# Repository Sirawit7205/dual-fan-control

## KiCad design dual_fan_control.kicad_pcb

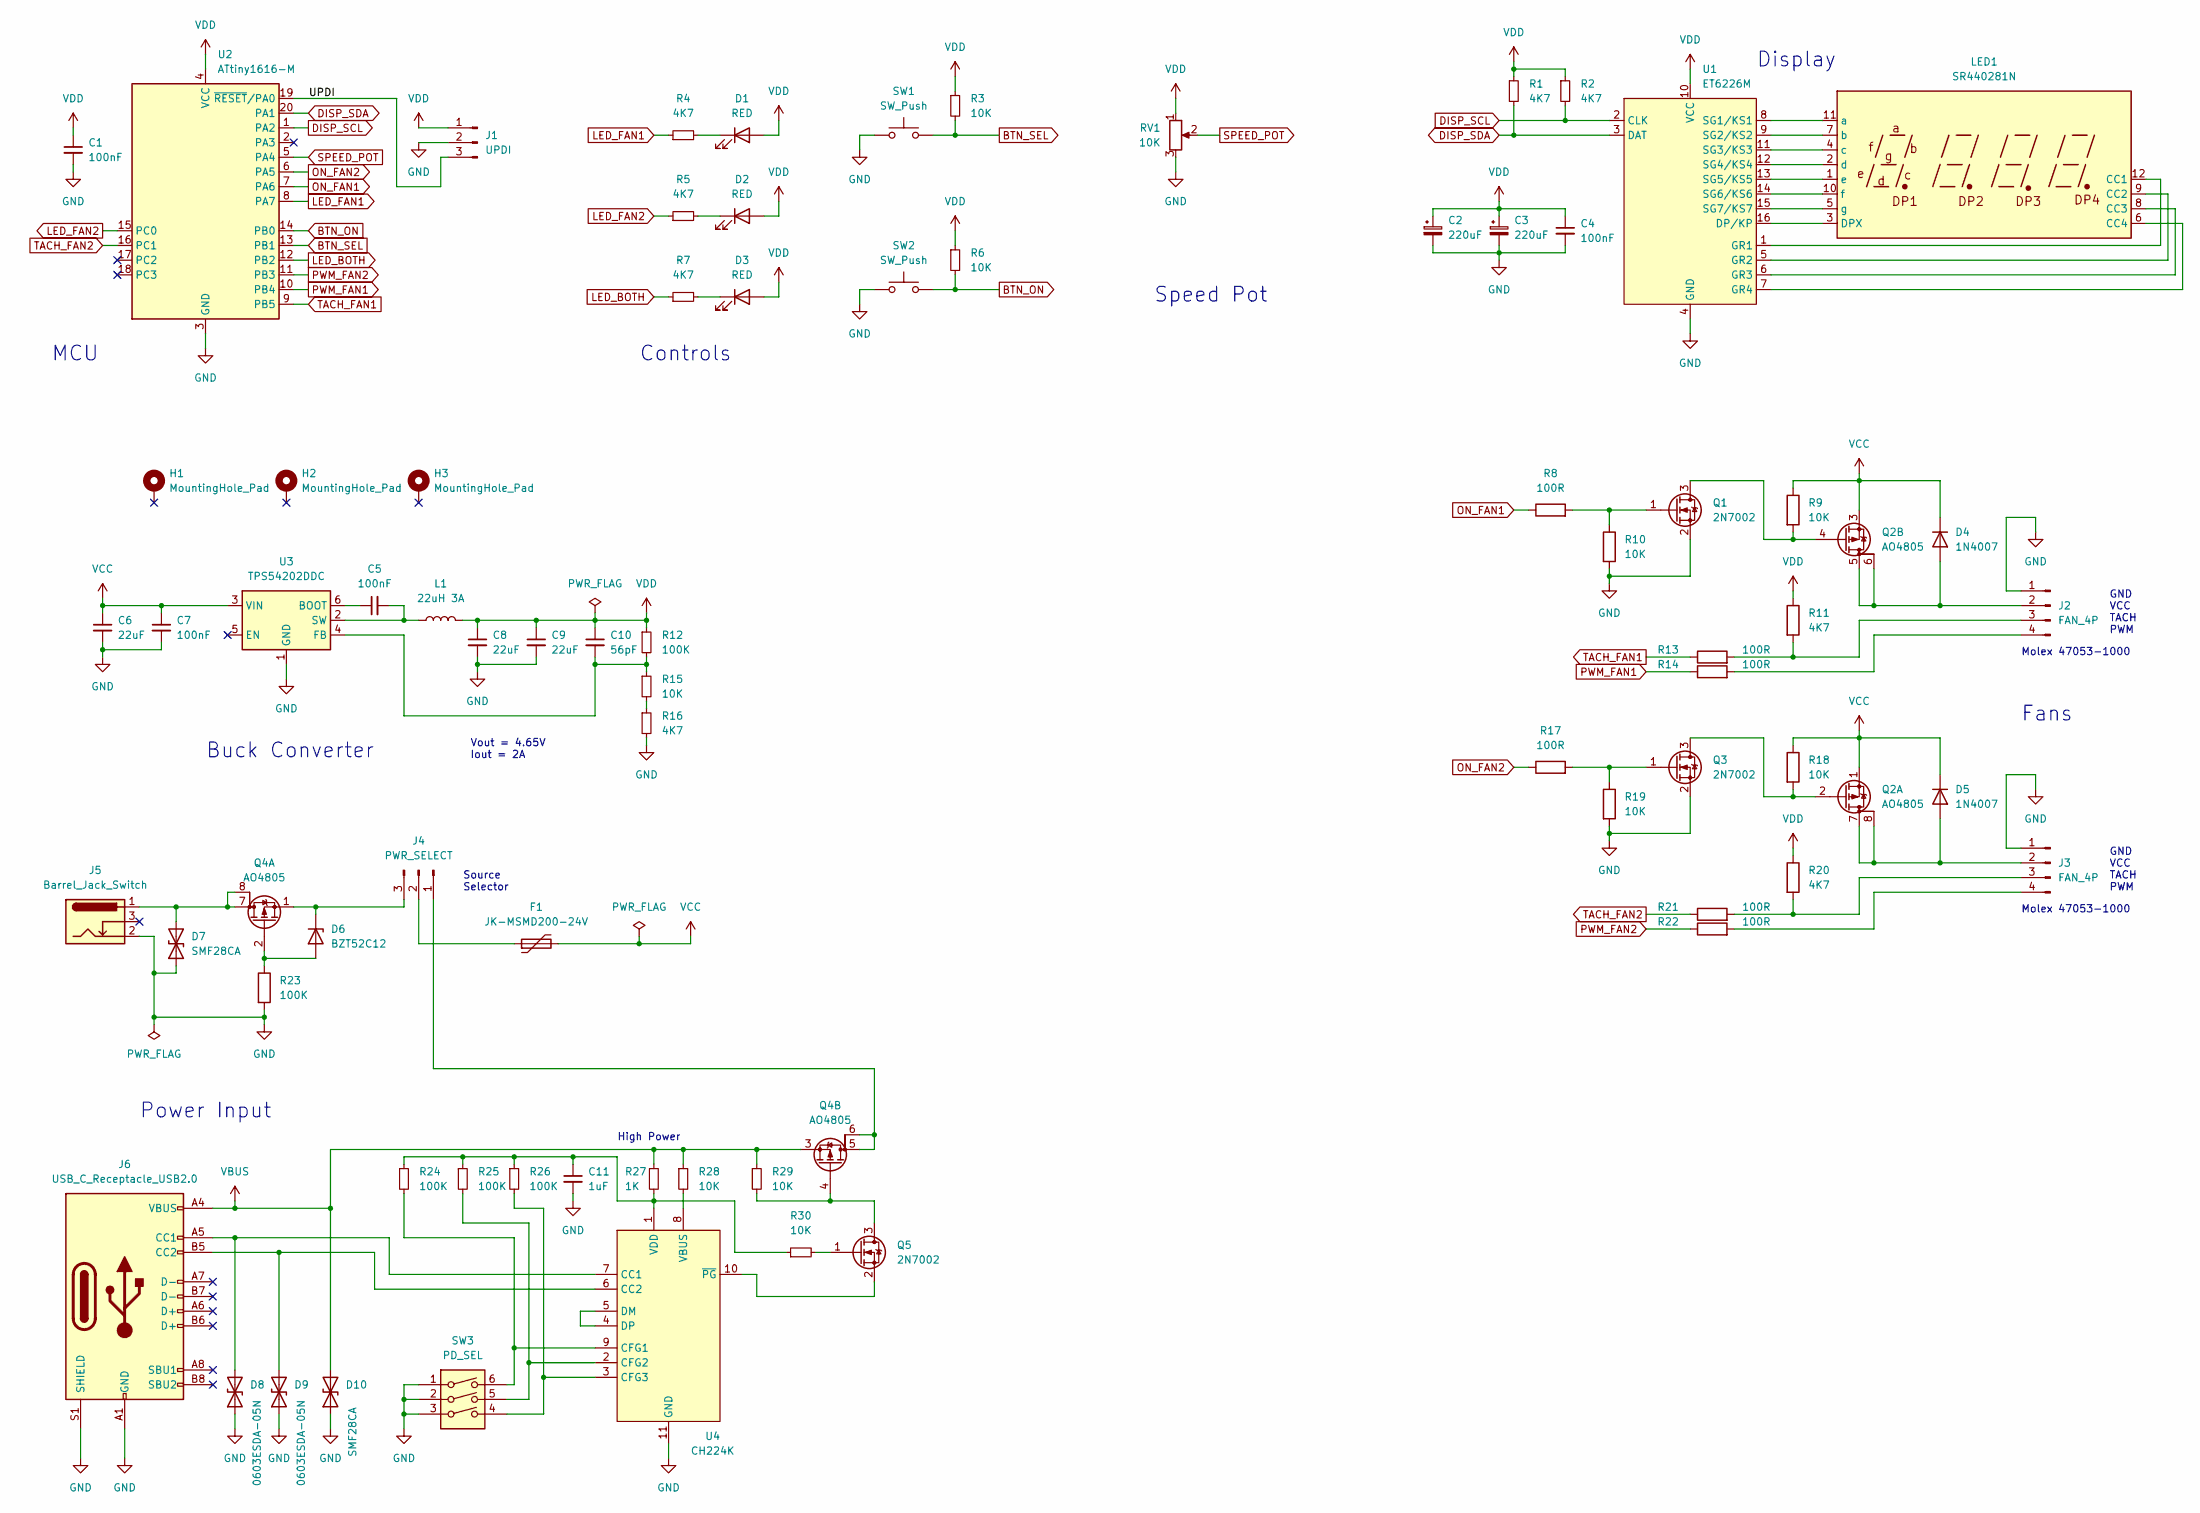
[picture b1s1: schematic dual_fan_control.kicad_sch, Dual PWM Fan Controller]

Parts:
C1, C4, C5, C7: 100nF; C_0603_1608Metric
C2, C3: 220uF; CP_EIA-3528-21_Kemet-B
C6, C8, C9: 22uF; C_1210_3225Metric
C10: 56pF; C_0603_1608Metric
C11: 1uF; C_0603_1608Metric
D1, D2, D3: RED; LED_0603_1608Metric
D4, D5: 1N4007; D_SOD-123F
D6: BZT52C12; D_SOD-323
D7, D10: SMF28CA; D_SOD-123F
D8, D9: 0603ESDA-05N; D_0603_1608Metric
F1: JK-MSMD200-24V; Fuse_1812_4532Metric_Pad1.30x3.40mm_HandSolder
H1, H2, H3: MountingHole_Pad; MountingHole_2.2mm_M2_DIN965_Pad
J1: UPDI; PinHeader_1x03_P2.54mm_Vertical
J2, J3: FAN_4P; Molex_KK-254_AE-6410-04A_1x04_P2.54mm_Vertical
J4: PWR_SELECT; PinHeader_1x03_P2.54mm_Vertical
J5: Barrel_Jack_Switch; BarrelJack_Horizontal_CircularHoles
J6: USB_C_Receptacle_USB2.0; USB_C_Receptacle_HRO_TYPE-C-31-M-12_NO_SBU_CircularHoles
L1: 22uH 3A; L_Bourns_SRN6045TA
LED1: SR440281N
Q1, Q3, Q5: 2N7002; SOT-23
Q2, Q4: AO4805; SOIC-8_3.9x4.9mm_P1.27mm
R1, R2, R4, R5, R7, R11, R16, R20: 4K7; R_0603_1608Metric
R3, R6, R9, R10, R15, R18, R19, R28, R29, R30: 10K; R_0603_1608Metric
R8, R13, R14, R17, R21, R22: 100R; R_0603_1608Metric
R12, R23, R24, R25, R26: 100K; R_0603_1608Metric
R27: 1K; R_1206_3216Metric
RV1: 10K; Potentiometer_Bourns_3386P_Vertical
SW1, SW2: SW_Push; SW_SPST_CK_RS282G05A3
SW3: PD_SEL; SW_DIP_SPSTx03_Slide_KingTek_DSHP03TS_W7.62mm_P1.27mm
U1: ET6226M; SOIC-16_3.9x9.9mm_P1.27mm
U2: ATtiny1616-M; VQFN-20-1EP_3x3mm_P0.4mm_EP1.7x1.7mm
U3: TPS54202DDC; SOT-23-6
U4: CH224K; ESSOP-10-1EP_3.9x4.9mm_P1.00mm_EP2.29x3mm

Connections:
/UPDI: J1.3, U2.19 (~RESET/PA0)
BTN_ON: R6.2, SW2.2, U2.14 (PB0)
BTN_SEL: R3.2, SW1.2, U2.13 (PB1)
DISP_SCL: R2.2, U1.2 (CLK), U2.1 (PA2)
DISP_SDA: R1.2, U1.3 (DAT), U2.20 (PA1)
GND: C1.2, C2.2, C3.2, C4.2, C6.2, C7.2, C8.2, C9.2, C11.2, D7.1 (A1), D8.1 (A1), D9.1 (A1), D10.1 (A1), J1.2, J2.1, J3.1, J5.2, J6.A1 (GND), J6.A12 (GND), J6.B1 (GND), J6.B12 (GND), J6.S1 (SHIELD), Q1.2 (S), Q3.2 (S), R10.2, R16.2, R19.2, R23.2, RV1.3, SW1.1, SW2.1, SW3.1, SW3.2, SW3.3, U1.4 (GND), U2.3 (GND), U2.21 (GND), U3.1 (GND), U4.11 (GND)
LED_BOTH: R7.1, U2.12 (PB2)
LED_FAN1: R4.1, U2.8 (PA7)
LED_FAN2: R5.1, U2.15 (PC0)
unnamed: C5.1, U3.6 (BOOT)
unnamed: C5.2, L1.1, U3.2 (SW)
unnamed: C10.2, R12.2, R15.1, U3.4 (FB)
unnamed: C11.1, R24.1, R25.1, R26.1, R27.2, R30.1, U4.1 (VDD)
unnamed: D1.1 (K), R4.2
unnamed: D2.1 (K), R5.2
unnamed: D3.1 (K), R7.2
unnamed: D4.2 (A), J2.2, Q2.5 (D), Q2.6 (G)
unnamed: D5.2 (A), J3.2, Q2.7 (D), Q2.8 (G)
unnamed: D6.1 (K), J4.3, Q4.1 (S)
unnamed: D6.2 (A), Q4.2 (G), R23.1
unnamed: D7.2 (A2), J5.1, Q4.7 (D), Q4.8 (G)
unnamed: D8.2 (A2), J6.A5 (CC1), U4.7 (CC1)
unnamed: D9.2 (A2), J6.B5 (CC2), U4.6 (CC2)
unnamed: F1.1, J4.2
unnamed: J2.3, R11.2, R13.2
unnamed: J2.4, R14.2
unnamed: J3.3, R20.2, R21.2
unnamed: J3.4, R22.2
unnamed: J4.1, Q4.5 (D), Q4.6 (G)
unnamed: LED1.1 (e), U1.13 (SG5/KS5)
unnamed: LED1.2 (d), U1.12 (SG4/KS4)
unnamed: LED1.3 (DPX), U1.16 (DP/KP)
unnamed: LED1.4 (c), U1.11 (SG3/KS3)
unnamed: LED1.5 (g), U1.15 (SG7/KS7)
unnamed: LED1.6 (CC4), U1.7 (GR4)
unnamed: LED1.7 (b), U1.9 (SG2/KS2)
unnamed: LED1.8 (CC3), U1.6 (GR3)
unnamed: LED1.9 (CC2), U1.5 (GR2)
unnamed: LED1.10 (f), U1.14 (SG6/KS6)
unnamed: LED1.11 (a), U1.8 (SG1/KS1)
unnamed: LED1.12 (CC1), U1.1 (GR1)
unnamed: Q1.1 (G), R8.2, R10.1
unnamed: Q1.3 (D), Q2.4 (G), R9.2
unnamed: Q2.2 (G), Q3.3 (D), R18.2
unnamed: Q3.1 (G), R17.2, R19.1
unnamed: Q4.4 (G), Q5.3 (D), R29.2
unnamed: Q5.1 (G), R30.2
unnamed: Q5.2 (S), U4.10 (~PG)
unnamed: R15.2, R16.1
unnamed: R24.2, SW3.6, U4.9 (CFG1)
unnamed: R25.2, SW3.5, U4.2 (CFG2)
unnamed: R26.2, SW3.4, U4.3 (CFG3)
unnamed: R28.2, U4.8 (VBUS)
unnamed: U4.4 (DP), U4.5 (DM)
ON_FAN1: R8.1, U2.7 (PA6)
ON_FAN2: R17.1, U2.6 (PA5)
PWM_FAN1: R14.1, U2.10 (PB4)
PWM_FAN2: R22.1, U2.11 (PB3)
SPEED_POT: RV1.2, U2.5 (PA4)
TACH_FAN1: R13.1, U2.9 (PB5)
TACH_FAN2: R21.1, U2.16 (PC1)
VBUS: D10.2 (A2), J6.A4 (VBUS), J6.A9 (VBUS), J6.B4 (VBUS), J6.B9 (VBUS), Q4.3 (S), R27.1, R28.1, R29.1
VCC: C6.1, C7.1, D4.1 (K), D5.1 (K), F1.2, Q2.1 (S), Q2.3 (S), R9.1, R18.1, U3.3 (VIN)
VDD: C1.1, C2.1, C3.1, C4.1, C8.1, C9.1, C10.1, D1.2 (A), D2.2 (A), D3.2 (A), J1.1, L1.2, R1.1, R2.1, R3.1, R6.1, R11.1, R12.1, R20.1, RV1.1, U1.10 (VCC), U2.4 (VCC)

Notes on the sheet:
Fans
Molex 47053-1000
GND VCC TACH PWM
High Power
MCU
Vout = 4.65V Iout = 2A
Display
Source Selector
Buck Converter
Controls
Speed Pot
Power Input

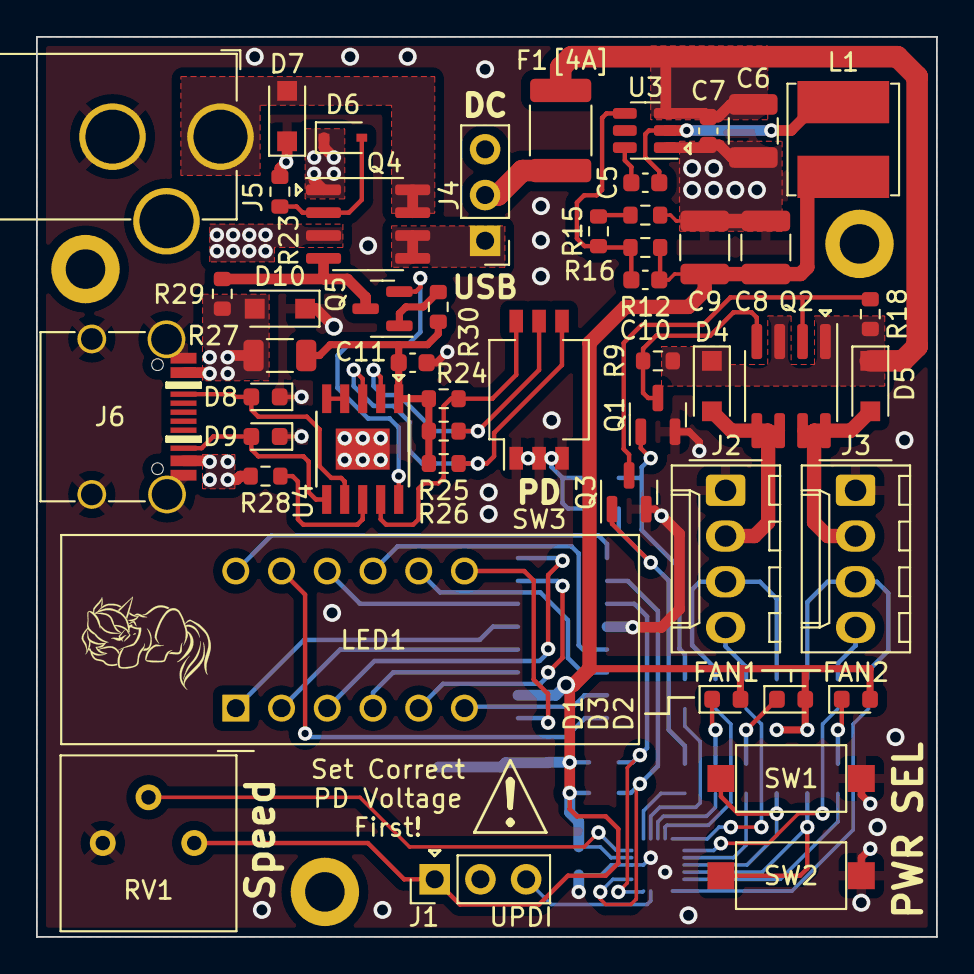
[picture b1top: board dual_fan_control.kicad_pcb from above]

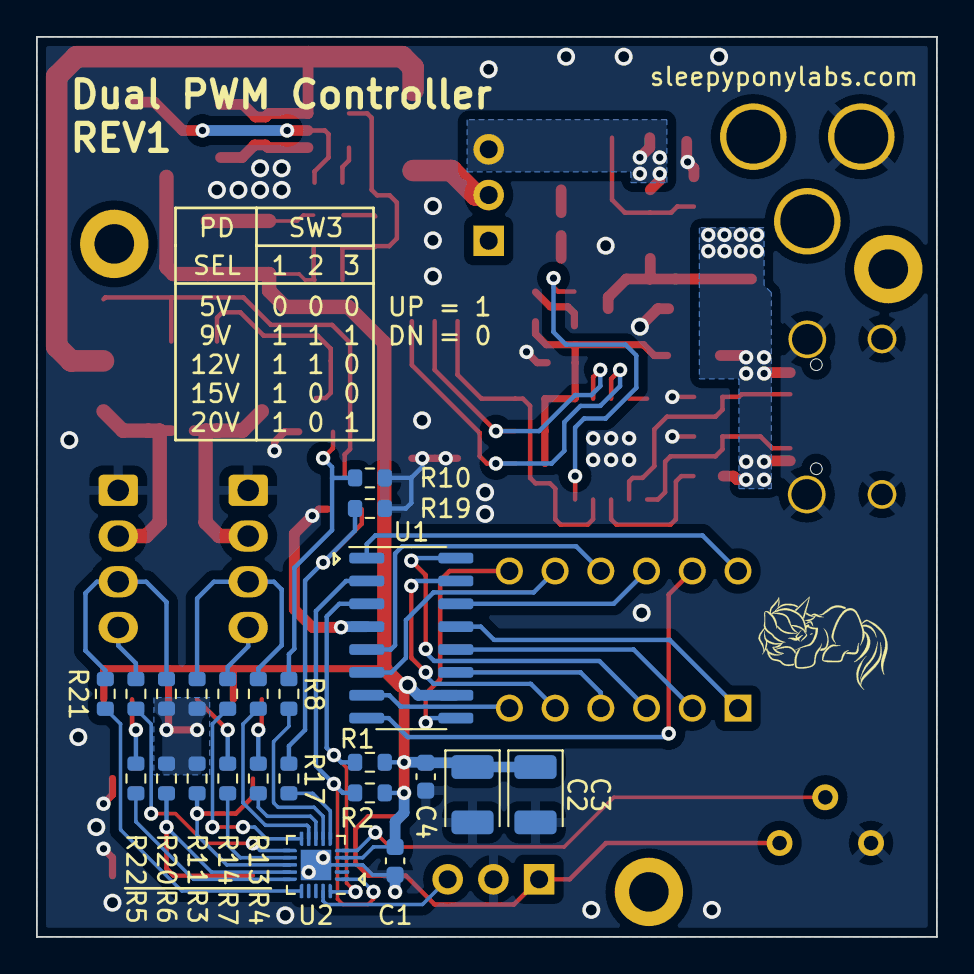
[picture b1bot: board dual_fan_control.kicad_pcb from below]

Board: 2 copper layers, 50.0 x 50.0 mm, 76 parts (23 on the bottom side), 64 nets.

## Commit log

2023-05-20 Minor adjustments
2023-05-21 Add IBOM
2023-06-11 Update IBOM
2023-08-16 Fix incorrect button net labels
2023-08-16 Add firmware code
2023-08-26 Fix tach speed measurement
2023-08-27 Code cleanup
2023-09-02 add scienfic notation output for fan speed over 9999 RPM
2023-09-10 Add proper user interface
2023-09-13 Add power % display and fixed PWM timer not running
